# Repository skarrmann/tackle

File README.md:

# Tackle Keyboard

Tackle is a wearable 48 key ortholinear keyboard, powered by a bluetooth-enabled Pro Micro compatible dev board.

It uses Choc v1 keyswitches with 18mm x 17mm spacing.

Tackle is strapped to your torso so you can type anywhere your hands are free.

[Typing demonstration video](https://youtu.be/kZD4jYyr6XI?si=NpnWW7PNuFhlqIOq)

## Project structure

* [`gerbers`](gerbers): Gerber files for PCB manufacturing
* [`graphics`](graphics): Source assets for PCB silkscreen
* [`kicad`](kicad): KiCad project files (schematics and PCB designs)
* [`kicad-libraries`](kicad-libraries): KiCad components and footprints
* [`images`](images): Images for project documentation

## PCBs

**Each build uses FIVE copies of the same PCB.**

One PCB is used as the logical PCB. All components are soldered on to this board.

Three PCBs are used as center plates to encase the microcontroller dev board and battery. Note the breakout sections of these PCBs must be cut out.

A final PCB is used as the bottom plate. All the PCBs are screwed directly together.

## Keyboard firmware

* ZMK
    * Tackle shield definition is in [skarrmann's zmk-config](https://github.com/skarrmann/zmk-config)

## Bill of materials

Part | Purpose | Quantity | Notes
---- | ------- | -------- | ---------
Main PCB  | logical PCB, case plates | 5 | Send Gerber zip files to [JLCPCB](https://jlcpcb.com/)
Bluetooth Pro Micro | Microcontroller board | 1 | nice!nano or SuperMini nRF52840
303450 LiPo Battery | Powers the wireless keyboard | 1 | JST PH 2.0 connector
S2B-PH-K-S connector | JST PH 2.0 battery connector | 1 |
SS12D00 | On/Off switch | 1 | Can also use E-Switch EG1218
6mm x 6mm push button | Reset button | 1 |
1N4148 SOD-123 | Diodes for keyboard row-column matrix | 48 |
Choc v1 Keyswitches |  | 48 |
Choc v1 Keycaps |  | 48 | Use keycaps which fit 18mm x 17mm spacing
M2 10mm screws | Screws PCBs together | 10 |
M2 nuts | Holds the top screws between the PCBs | 10 |
[Peel-a-way Sockets and Pins](https://ringerkeys.com/collections/modders-tools/products/peel-a-way-sockets) | Sockets the dev board to PCB | 2 strips of 12 pins/sockets | May use other low profile sockets which give no more than ~4.5 mm total height.
40mm/1.5" nylon strapping, buckles, and slide clips set | Straps the keyboard to your torso | 1 | [Example nylon webbing set](https://www.amazon.com/dp/B09FFKCLD7?ref=ppx_yo2ov_dt_b_fed_asin_title)

## PCB manufacturing settings

These are the manufacturing settings I used when ordering from JLCPCB:

* **Base Material**: FR4
* **Layers**: 2
* **Dimensions**: (whatever the gerber file specifies)
* **PCB Qty**: 5
* **Different Design**: 1
* **Delivery Format**: Single PCB
* **PCB Thickness**: 1.6
* **PCB Color**: Black
* **Silkscreen**: White
* **Surface Finish**: LeadFree HASL-RoHS
* **Outer Copper Weight**: 1 oz
* **Gold Fingers**: No
* **Confirm Production File**: No
* **Flying Probe Test**: Fully Test
* **Castellated Holes**: No
* **Mark on PCB**: Remove Mark

## Build tips

* Before starting, check if the PCBs are warped, and bend them to be perfectly flat before soldering.
* First, cut the battery and dev board sections out of the three center plate PCBs. I used a 10" mini hacksaw. **CUT PCBs OUTSIDE WHILE WEARING A MASK. PCB DUST IS HAZARDOUS FOR YOUR LUNGS.**
    * 
    * 
* Next, solder the dev board sockets, diodes, and battery connector. Make sure the diodes are oriented correctly, cathode on the side with the line! After the keyswitches are soldered in, you won't be able to get to the diodes anymore.
    * 
    * 
    * 
* Then solder the keyswitches.
    * 
* After soldering the keyswitches, use flush cutters to clip down the metal pins on the two keyswitches underneath the dev board. Make sure the dev board is placed **components side up**. The pinout labels printed on the PCB should align with those printed on the dev board. 
    * 
* Then solder the power switch and reset button.
    * 
* Line up the three center plate PCBs. Place the battery in the center hole, and route the battery wires in the empty space near the battery connector. **MAKE SURE THE BLACK WIRE LINES UP WITH THE (-), AND THE RED WIRE LINES UP WITH THE (+), OR YOU'LL FRY YOUR DEV BOARD!**
    * 
* Line up the bottom plate PCB. Put the M2 screws through the bottom of the PCBs, and secure them at the top of the PCBs with an M2 nut.
    * 
    * 

## Revision history

* Tackle 1.1 (2024-12-13)
    * Widen breakout lines for dev board and battery, to make sawing PCBs easier
* Tackle 1.0 (2024-11-28)
    * Initial Choc switch PCB design

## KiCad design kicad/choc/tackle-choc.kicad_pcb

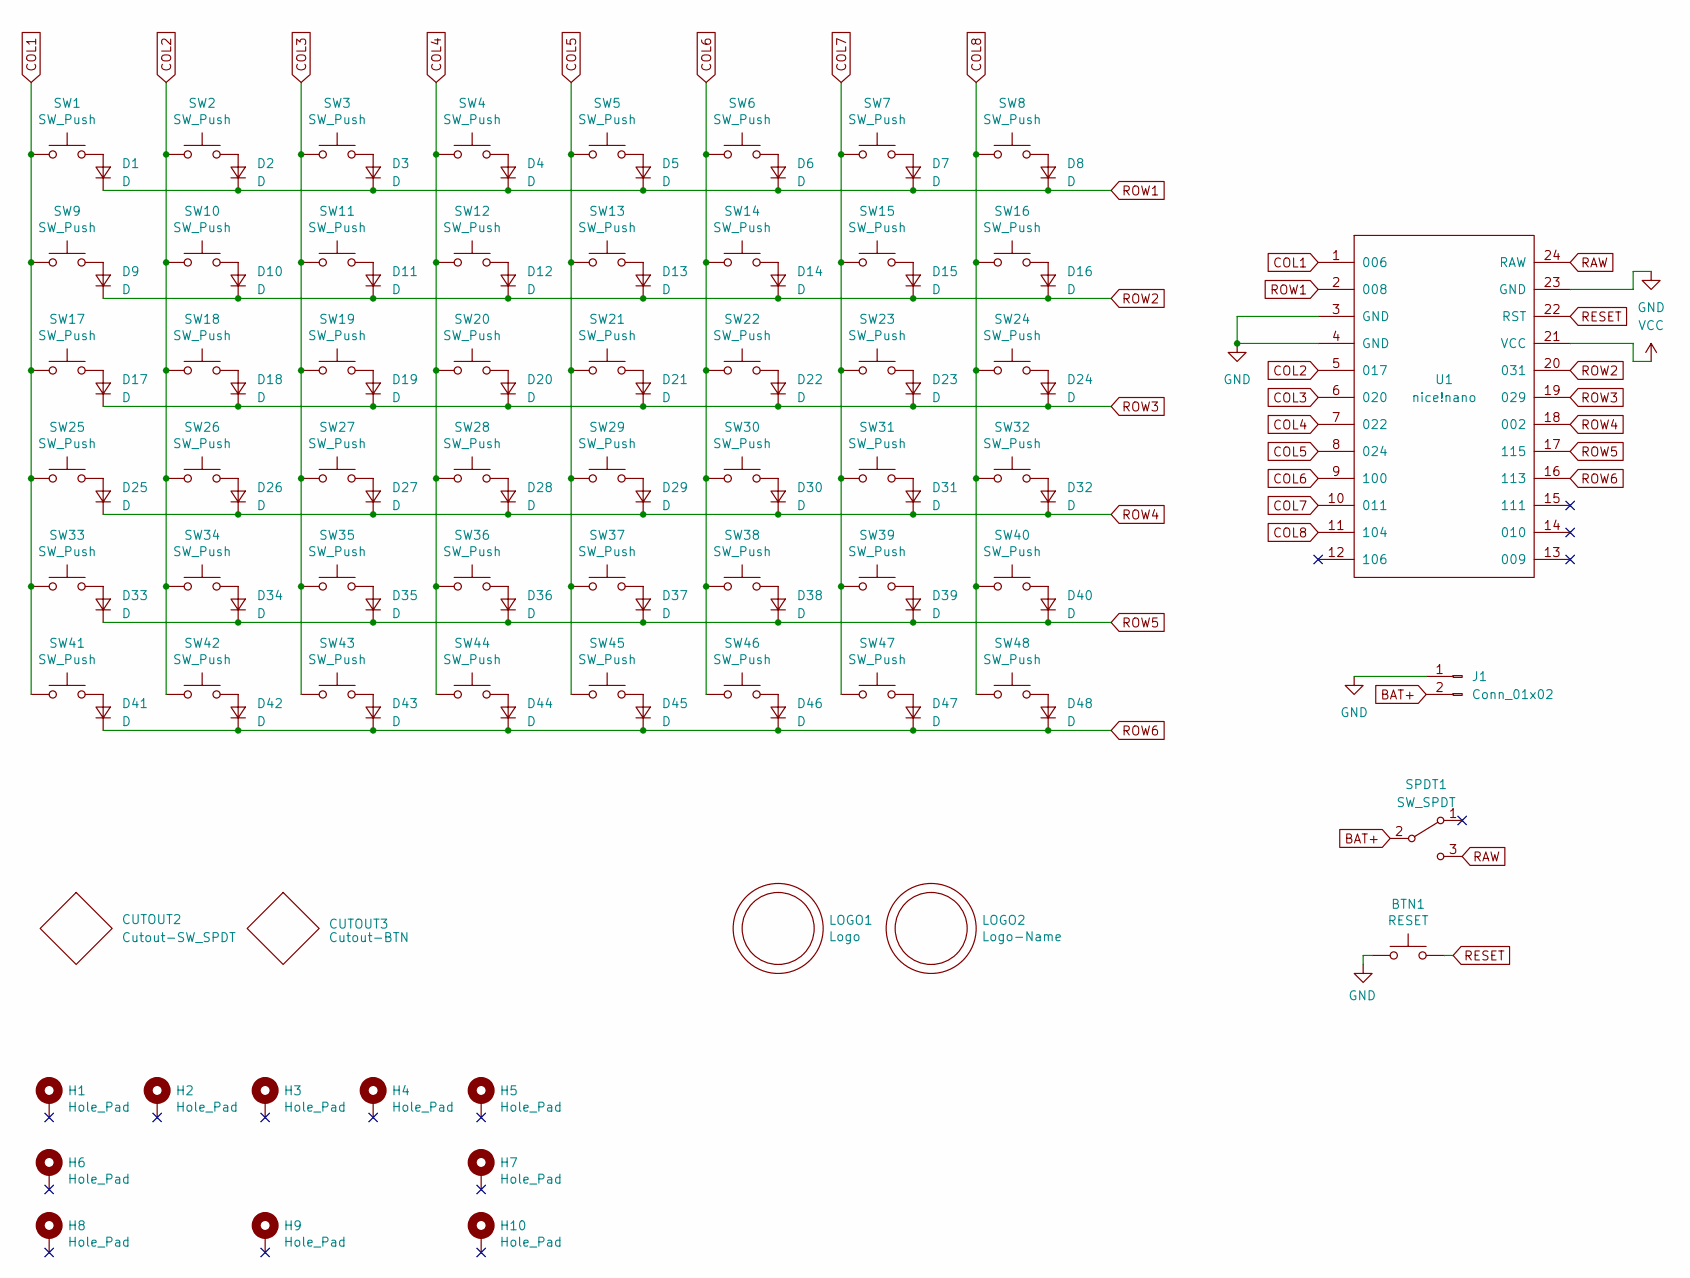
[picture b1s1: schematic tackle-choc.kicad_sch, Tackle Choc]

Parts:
BTN1: RESET; SW_Push_6mm
CUTOUT2: Cutout-SW_SPDT; Cutout_SW_SS12D00
CUTOUT3: Cutout-BTN; Cutout_SW_Push_6mm
D1, D2, D3, D4, D5, D6, D7, D8, D9, D10, D11, D12, D13, D14, D15, D16, D17, D18, D19, D20, D21, D22, D23, D24, D25, D26, D27, D28, D29, D30, D31, D32, D33, D34, D35, D36, D37, D38, D39, D40, D41, D42, D43, D44, D45, D46, D47, D48: D; D_SOD-123
H1, H2, H3, H4, H5, H6, H7, H8, H9, H10: Hole_Pad; Mount_M2
J1: Conn_01x02; JST_PH_S2B-PH-K_1x02_P2.00mm_Horizontal
LOGO1: Logo; Logo_Tackle
LOGO2: Logo-Name; Logo_Tackle_Name
SPDT1: SW_SPDT; SW_SS12D00
SW1, SW2, SW3, SW4, SW5, SW6, SW7, SW8, SW9, SW10, SW11, SW12, SW13, SW14, SW15, SW16, SW17, SW18, SW19, SW20, SW21, SW22, SW23, SW24, SW25, SW26, SW27, SW28, SW29, SW30, SW31, SW32, SW33, SW34, SW35, SW36, SW37, SW38, SW39, SW40, SW41, SW42, SW43, SW44, SW45, SW46, SW47, SW48: SW_Push; SW_Choc
U1: nice!nano

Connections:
BAT+: J1.2, SPDT1.2 (B)
COL1: SW1.1, SW9.1, SW17.1, SW25.1, SW33.1, SW41.1, U1.1 (006)
COL2: SW2.1, SW10.1, SW18.1, SW26.1, SW34.1, SW42.1, U1.5 (017)
COL3: SW3.1, SW11.1, SW19.1, SW27.1, SW35.1, SW43.1, U1.6 (020)
COL4: SW4.1, SW12.1, SW20.1, SW28.1, SW36.1, SW44.1, U1.7 (022)
COL5: SW5.1, SW13.1, SW21.1, SW29.1, SW37.1, SW45.1, U1.8 (024)
COL6: SW6.1, SW14.1, SW22.1, SW30.1, SW38.1, SW46.1, U1.9 (100)
COL7: SW7.1, SW15.1, SW23.1, SW31.1, SW39.1, SW47.1, U1.10 (011)
COL8: SW8.1, SW16.1, SW24.1, SW32.1, SW40.1, SW48.1, U1.11 (104)
GND: BTN1.2, J1.1, U1.3 (GND), U1.4 (GND), U1.23 (GND)
unnamed: D1.2 (A), SW1.2
unnamed: D2.2 (A), SW2.2
unnamed: D3.2 (A), SW3.2
unnamed: D4.2 (A), SW4.2
unnamed: D5.2 (A), SW5.2
unnamed: D6.2 (A), SW6.2
unnamed: D7.2 (A), SW7.2
unnamed: D8.2 (A), SW8.2
unnamed: D9.2 (A), SW9.2
unnamed: D10.2 (A), SW10.2
unnamed: D11.2 (A), SW11.2
unnamed: D12.2 (A), SW12.2
unnamed: D13.2 (A), SW13.2
unnamed: D14.2 (A), SW14.2
unnamed: D15.2 (A), SW15.2
unnamed: D16.2 (A), SW16.2
unnamed: D17.2 (A), SW17.2
unnamed: D18.2 (A), SW18.2
unnamed: D19.2 (A), SW19.2
unnamed: D20.2 (A), SW20.2
unnamed: D21.2 (A), SW21.2
unnamed: D22.2 (A), SW22.2
unnamed: D23.2 (A), SW23.2
unnamed: D24.2 (A), SW24.2
unnamed: D25.2 (A), SW25.2
unnamed: D26.2 (A), SW26.2
unnamed: D27.2 (A), SW27.2
unnamed: D28.2 (A), SW28.2
unnamed: D29.2 (A), SW29.2
unnamed: D30.2 (A), SW30.2
unnamed: D31.2 (A), SW31.2
unnamed: D32.2 (A), SW32.2
unnamed: D33.2 (A), SW33.2
unnamed: D34.2 (A), SW34.2
unnamed: D35.2 (A), SW35.2
unnamed: D36.2 (A), SW36.2
unnamed: D37.2 (A), SW37.2
unnamed: D38.2 (A), SW38.2
unnamed: D39.2 (A), SW39.2
unnamed: D40.2 (A), SW40.2
unnamed: D41.2 (A), SW41.2
unnamed: D42.2 (A), SW42.2
unnamed: D43.2 (A), SW43.2
unnamed: D44.2 (A), SW44.2
unnamed: D45.2 (A), SW45.2
unnamed: D46.2 (A), SW46.2
unnamed: D47.2 (A), SW47.2
unnamed: D48.2 (A), SW48.2
RAW: SPDT1.3 (C), U1.24 (RAW)
RESET: BTN1.1, U1.22 (RST)
ROW1: D1.1 (K), D2.1 (K), D3.1 (K), D4.1 (K), D5.1 (K), D6.1 (K), D7.1 (K), D8.1 (K), U1.2 (008)
ROW2: D9.1 (K), D10.1 (K), D11.1 (K), D12.1 (K), D13.1 (K), D14.1 (K), D15.1 (K), D16.1 (K), U1.20 (031)
ROW3: D17.1 (K), D18.1 (K), D19.1 (K), D20.1 (K), D21.1 (K), D22.1 (K), D23.1 (K), D24.1 (K), U1.19 (029)
ROW4: D25.1 (K), D26.1 (K), D27.1 (K), D28.1 (K), D29.1 (K), D30.1 (K), D31.1 (K), D32.1 (K), U1.18 (002)
ROW5: D33.1 (K), D34.1 (K), D35.1 (K), D36.1 (K), D37.1 (K), D38.1 (K), D39.1 (K), D40.1 (K), U1.17 (115)
ROW6: D41.1 (K), D42.1 (K), D43.1 (K), D44.1 (K), D45.1 (K), D46.1 (K), D47.1 (K), D48.1 (K), U1.16 (113)
VCC: U1.21 (VCC)

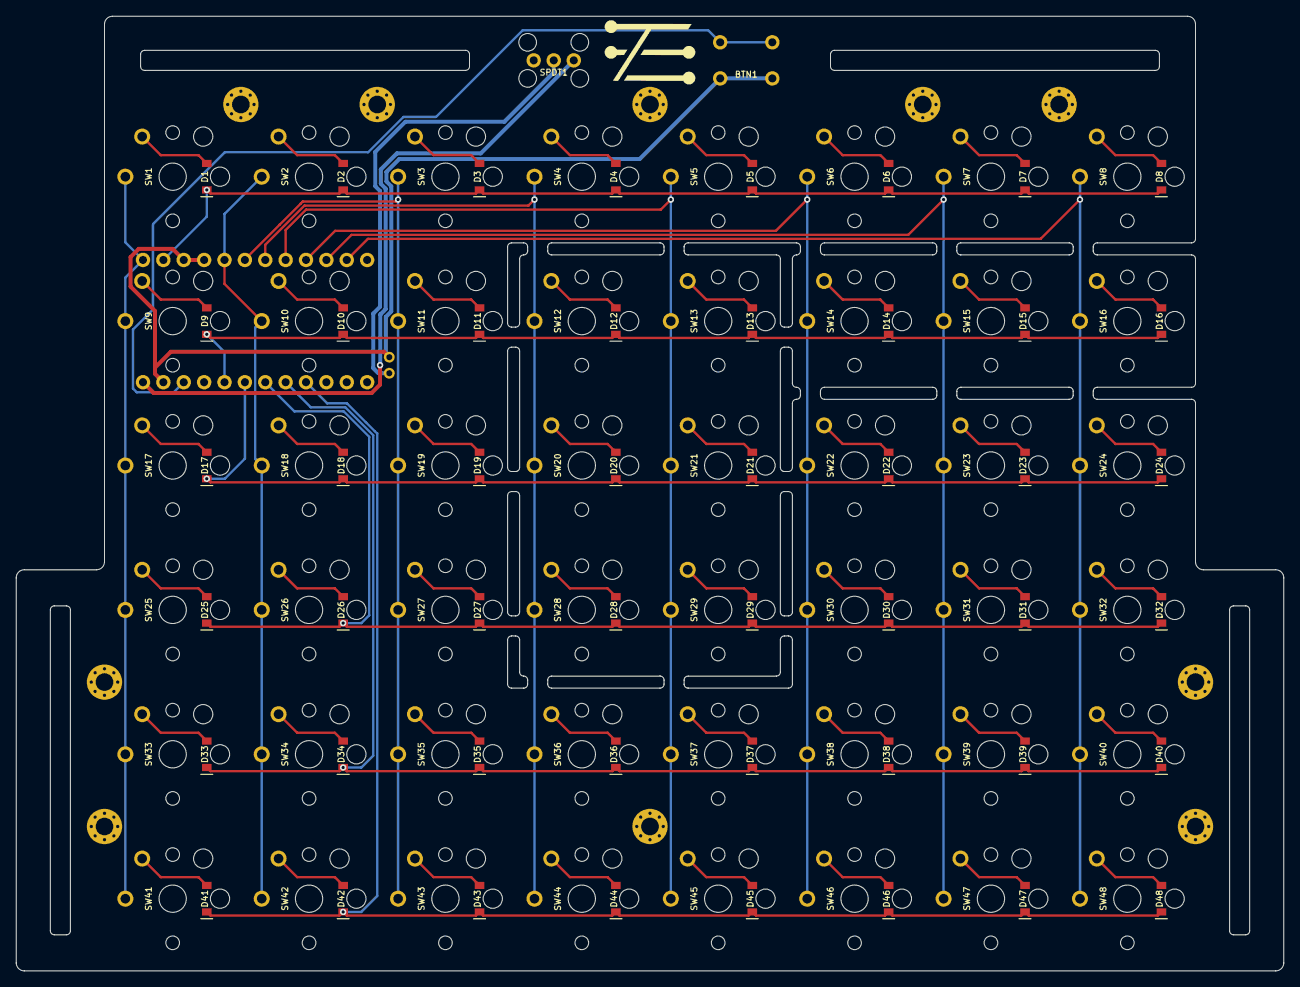
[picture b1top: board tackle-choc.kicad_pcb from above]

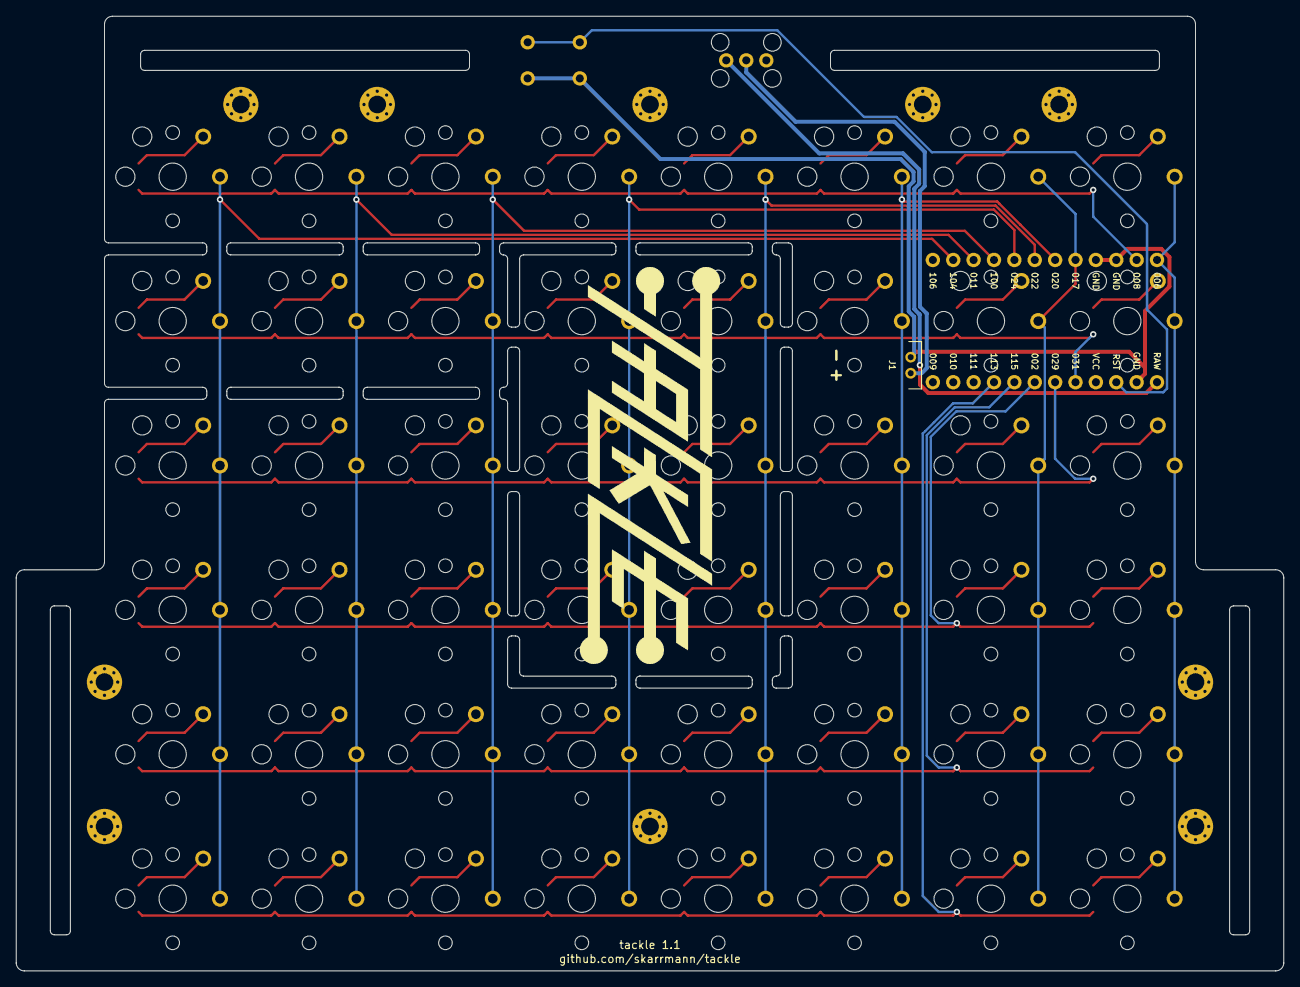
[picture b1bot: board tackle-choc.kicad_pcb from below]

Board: 2 copper layers, 158.0 x 119.0 mm, 114 parts (3 on the bottom side), 66 nets.

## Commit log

2024-11-27 Create Tackle keyboard
2024-11-27 Swap power switch direction, update fabrication settings
2024-11-28 Adjust board cuts and battery connector position
2024-12-12 Adjust strap slot sizes
2024-12-14 1.1 - widen cutouts to make sawing PCBs easier
2024-12-17 Add full build photos and link to typing demonstration video
